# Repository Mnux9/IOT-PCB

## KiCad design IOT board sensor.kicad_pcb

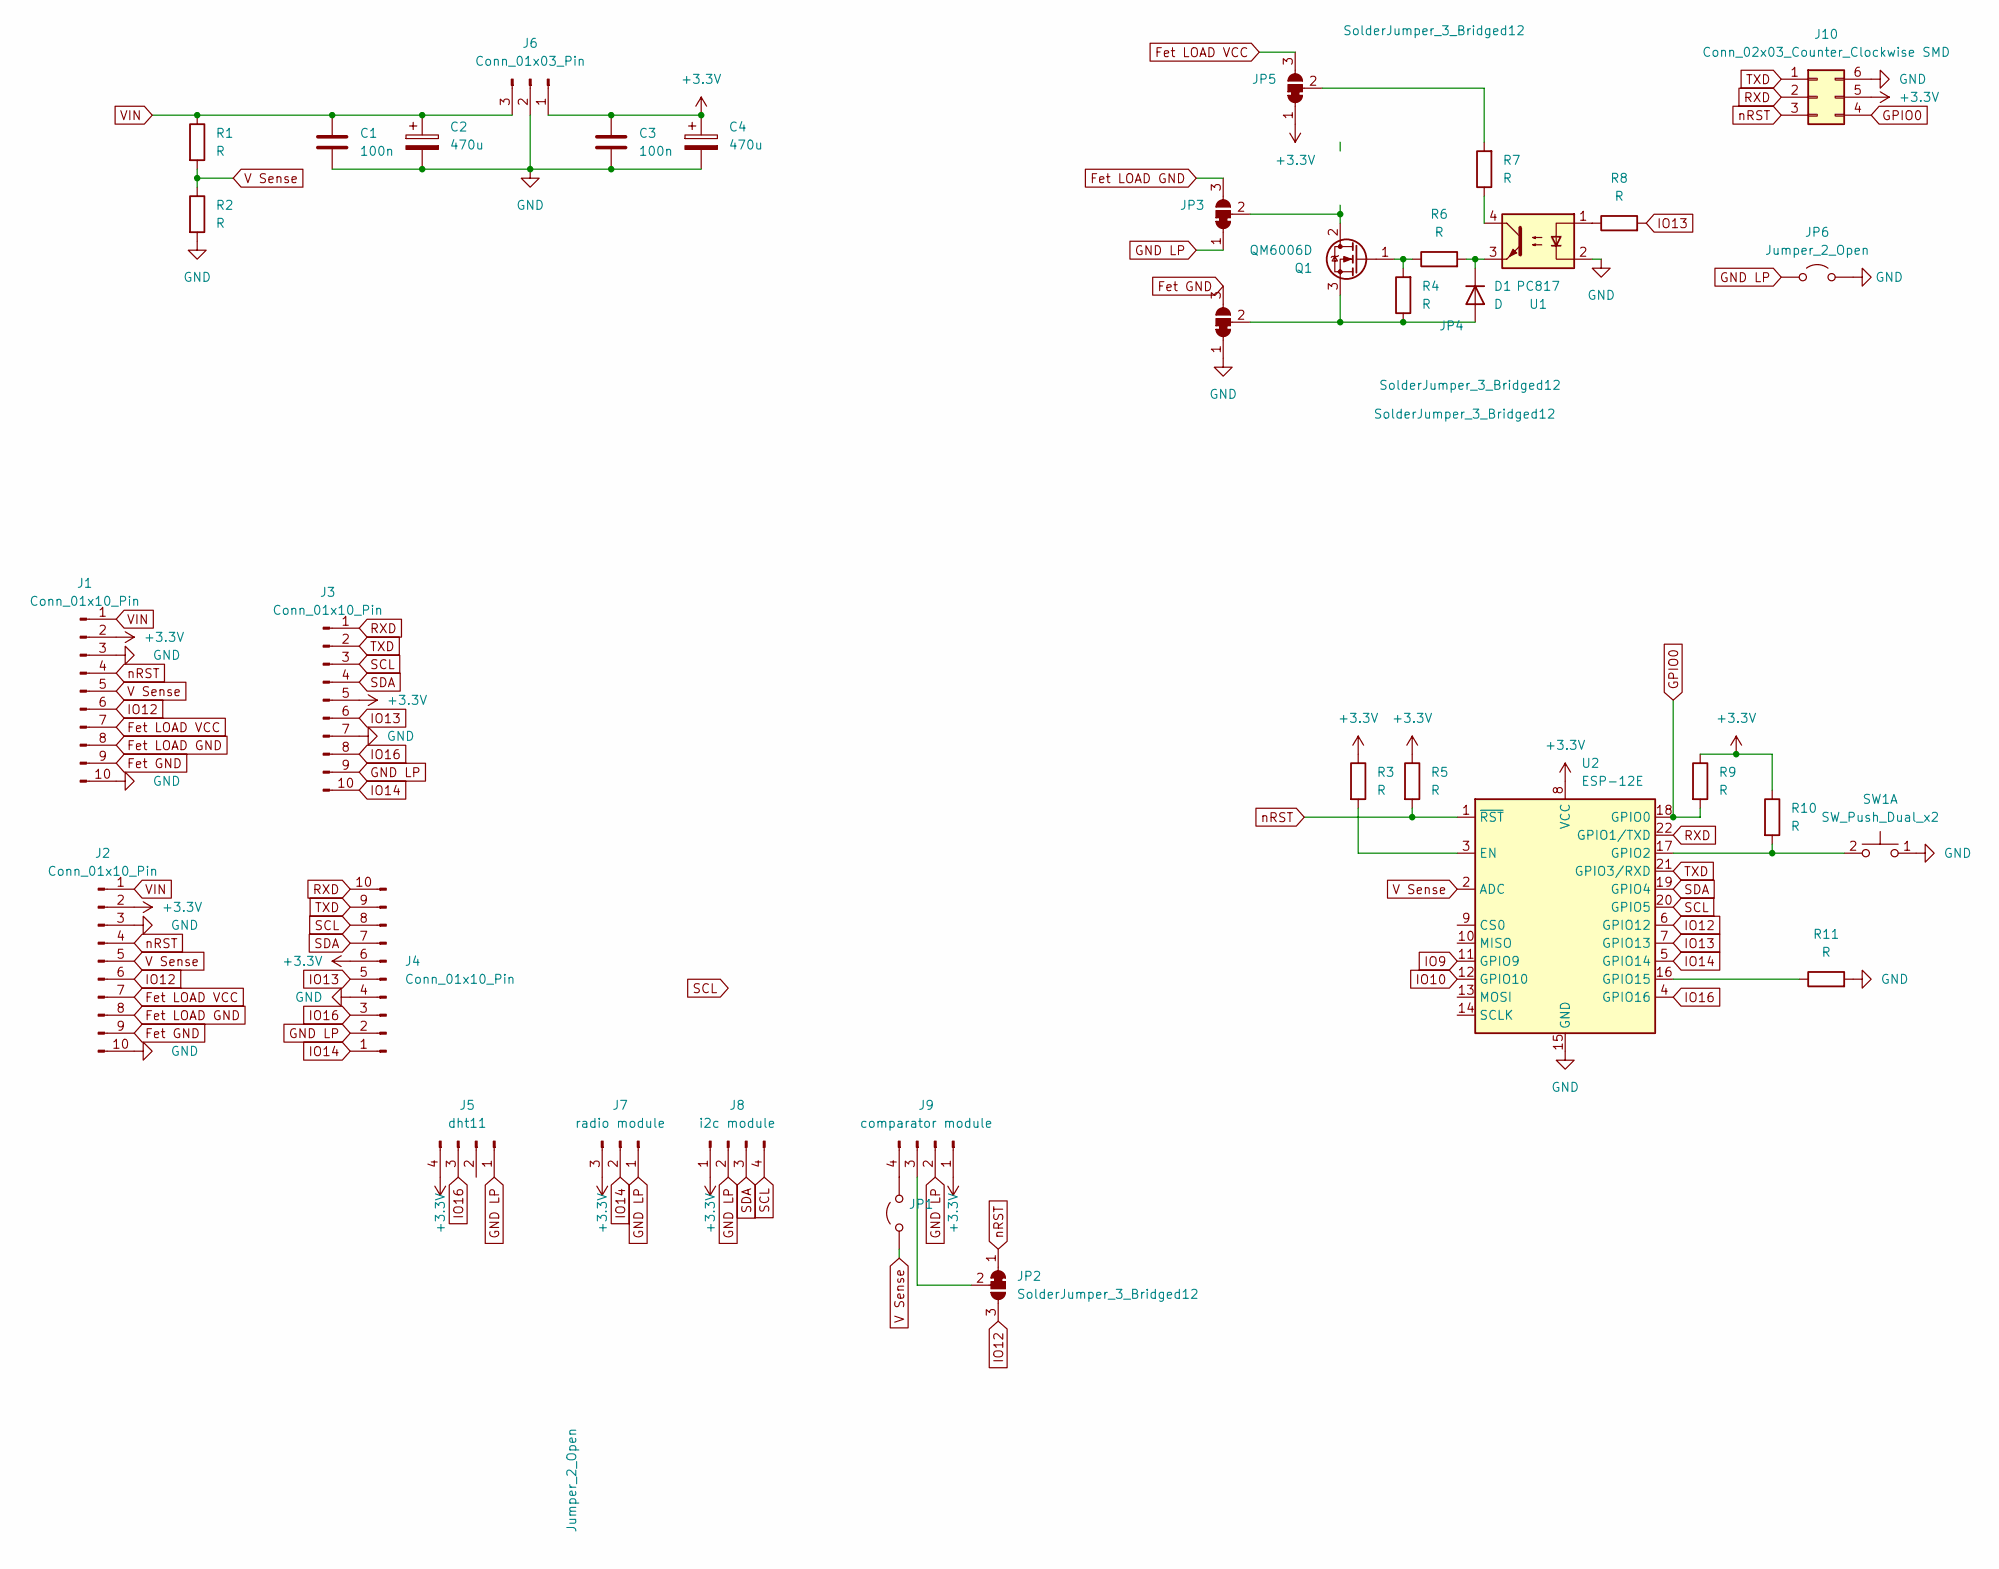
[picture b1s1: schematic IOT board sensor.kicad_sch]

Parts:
C1, C3: 100n; C_0805_2012Metric_Pad1.18x1.45mm_HandSolder
C2, C4: 470u; C_0805_2012Metric_Pad1.18x1.45mm_HandSolder
D1: D; D_0805_2012Metric_Pad1.15x1.40mm_HandSolder
J1, J3: Conn_01x10_Pin; PinHeader_1x10_P2.54mm_Vertical
J2, J4: Conn_01x10_Pin; TerminalBlock_4Ucon_1x10_P3.50mm_Horizontal
J5: dht11; PinHeader_1x04_P2.54mm_Vertical
J6: Conn_01x03_Pin; PinHeader_1x03_P2.54mm_Vertical
J7: radio module; PinHeader_1x03_P2.54mm_Vertical
J8: i2c module; PinHeader_1x04_P2.54mm_Vertical
J9: comparator module; PinHeader_1x04_P2.54mm_Vertical
J10: Conn_02x03_Counter_Clockwise SMD; PinHeader_2x03_P2.54mm_Vertical_SMD
JP1, JP6: Jumper_2_Open; SolderJumper-2_P1.3mm_Open_RoundedPad1.0x1.5mm
JP2, JP3, JP4, JP5: SolderJumper_3_Bridged12; SolderJumper-3_P1.3mm_Bridged2Bar12_RoundedPad1.0x1.5mm_Num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
Q1: QM6006D; TO-252-2
R1, R2, R3, R4, R5, R6, R7, R8, R9, R10, R11: R; R_0805_2012Metric_Pad1.20x1.40mm_HandSolder
SW1: SW_Push_Dual_x2; SW_PUSH_6mm
U1: PC817; DIP-4_W7.62mm_SMDSocket_SmallPads
U2: ESP-12E

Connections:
+3.3V: C3.1, C4.1, J1.2, J2.2, J3.5, J4.6, J5.4, J6.1, J7.3, J8.1, J9.1, J10.5, JP5.1 (A), R3.1, R5.1, R9.1, R10.1, U2.8 (VCC)
Fet GND: J1.9, J2.9, JP4.3 (B)
Fet LOAD GND: J1.8, J2.8, JP3.3 (B)
Fet LOAD VCC: J1.7, J2.7, JP5.3 (B)
GND: C1.2, C2.2, C3.2, C4.2, J1.3, J1.10, J2.3, J2.10, J3.7, J4.4, J6.2, J10.6, JP4.1 (A), JP6.2 (B), R2.2, R11.2, SW1.1 (C), U1.2, U2.15 (GND)
GND LP: J3.9, J4.2, J5.1, J7.1, J8.2, J9.2, JP3.1 (A), JP6.1 (A)
GPIO0: J10.4, R9.2, U2.18 (GPIO0)
IO9: U2.11 (GPIO9)
IO10: U2.12 (GPIO10)
IO12: J1.6, J2.6, JP2.3 (B), U2.6 (GPIO12)
IO13: J3.6, J4.5, R8.2, U2.7 (GPIO13)
IO14: J3.10, J4.1, J7.2, U2.5 (GPIO14)
IO16: J3.8, J4.3, J5.3, U2.4 (GPIO16)
unnamed: D1.2 (A), JP4.2 (C), Q1.3 (S), R4.1
unnamed: D1.1 (K), R6.2, U1.3
unnamed: J9.3, JP2.2 (C)
unnamed: J9.4, JP1.2 (B)
unnamed: JP3.2 (C), Q1.2 (D)
unnamed: JP5.2 (C), R7.2
unnamed: Q1.1 (G), R4.2, R6.1
unnamed: R7.1, U1.4
unnamed: R8.1, U1.1
unnamed: R10.2, SW1.2 (D), U2.17 (GPIO2)
unnamed: R3.2, U2.3 (EN)
unnamed: R11.1, U2.16 (GPIO15)
RXD: J3.1, J4.10, J10.2, U2.22 (GPIO1/TXD)
SCL: J3.3, J4.8, J8.4, U2.20 (GPIO5)
SDA: J3.4, J4.7, J8.3, U2.19 (GPIO4)
TXD: J3.2, J4.9, J10.1, U2.21 (GPIO3/RXD)
V Sense: J1.5, J2.5, JP1.1 (A), R1.2, R2.1, U2.2 (ADC)
VIN: C1.1, C2.1, J1.1, J2.1, J6.3, R1.1
nRST: J1.4, J2.4, J10.3, JP2.1 (A), R5.2, U2.1 (~RST)

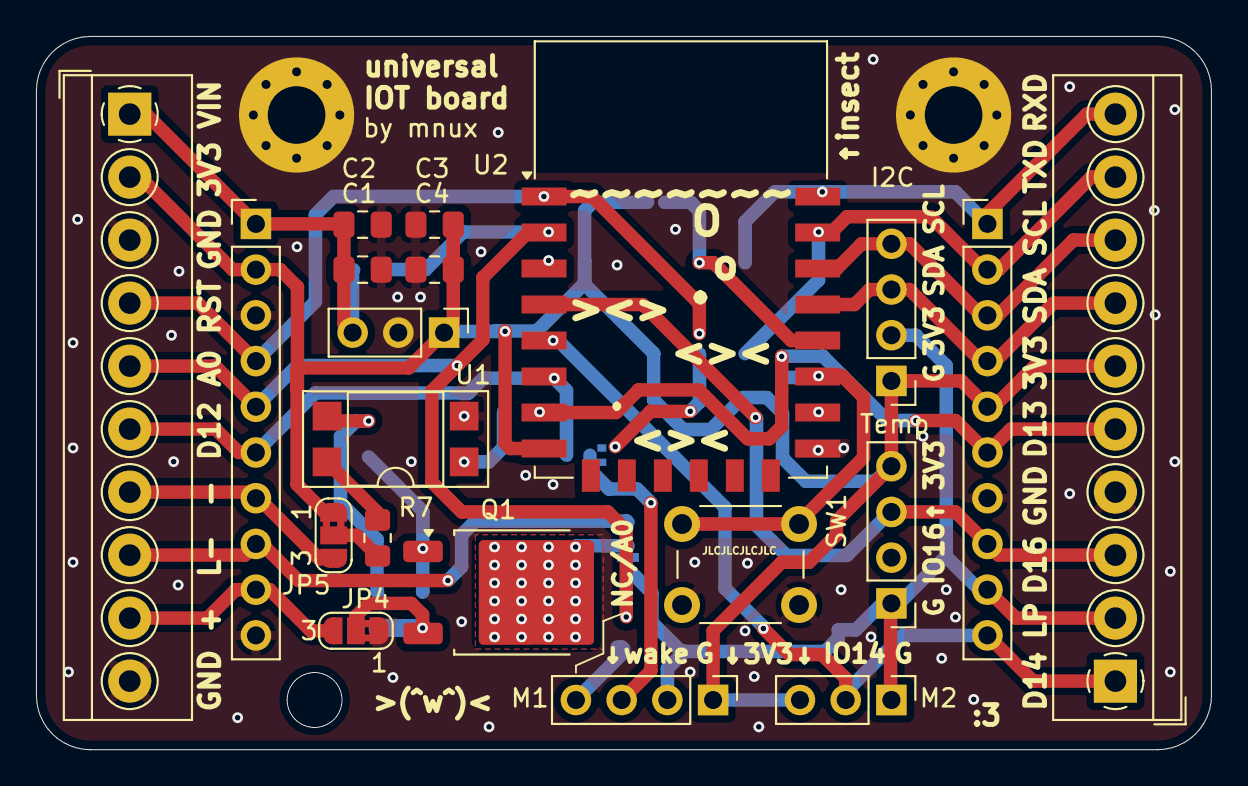
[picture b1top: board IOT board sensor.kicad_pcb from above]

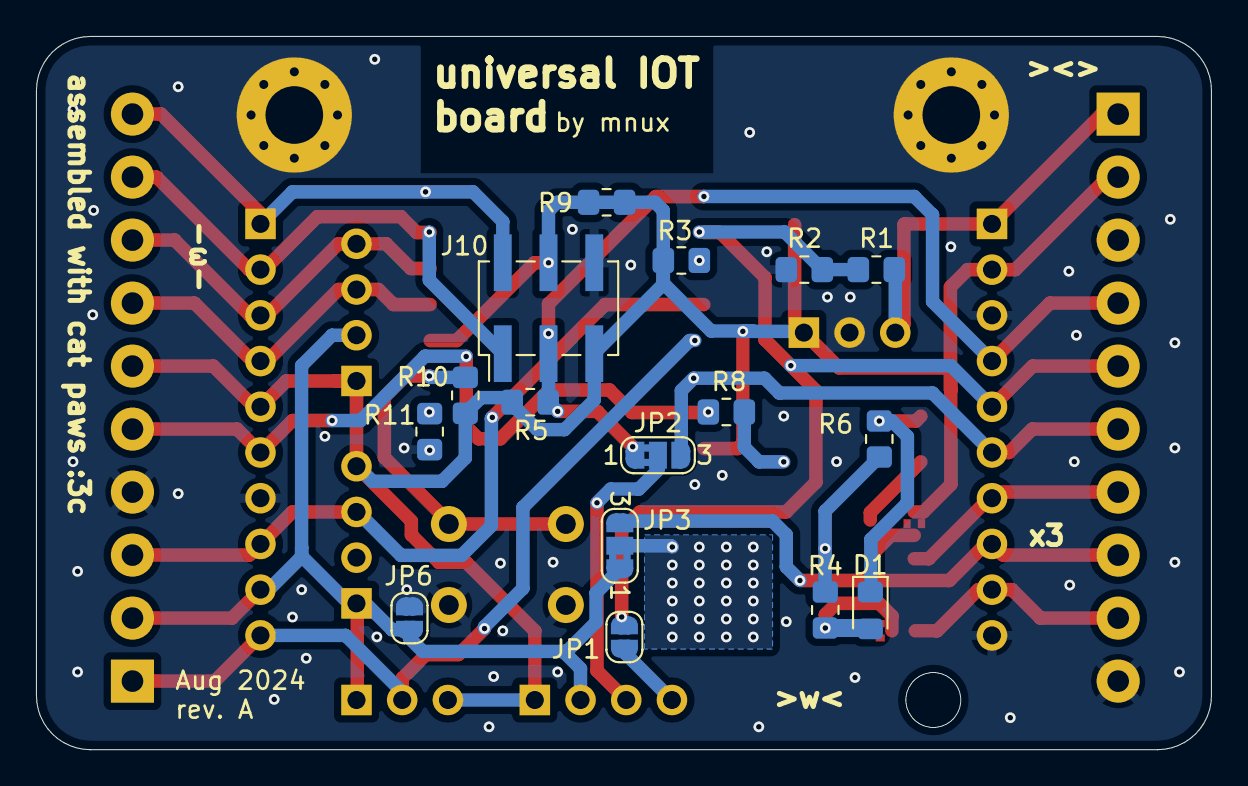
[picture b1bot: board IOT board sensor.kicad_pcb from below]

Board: 2 copper layers, 65.3 x 39.6 mm, 36 parts (16 on the bottom side), 30 nets.
